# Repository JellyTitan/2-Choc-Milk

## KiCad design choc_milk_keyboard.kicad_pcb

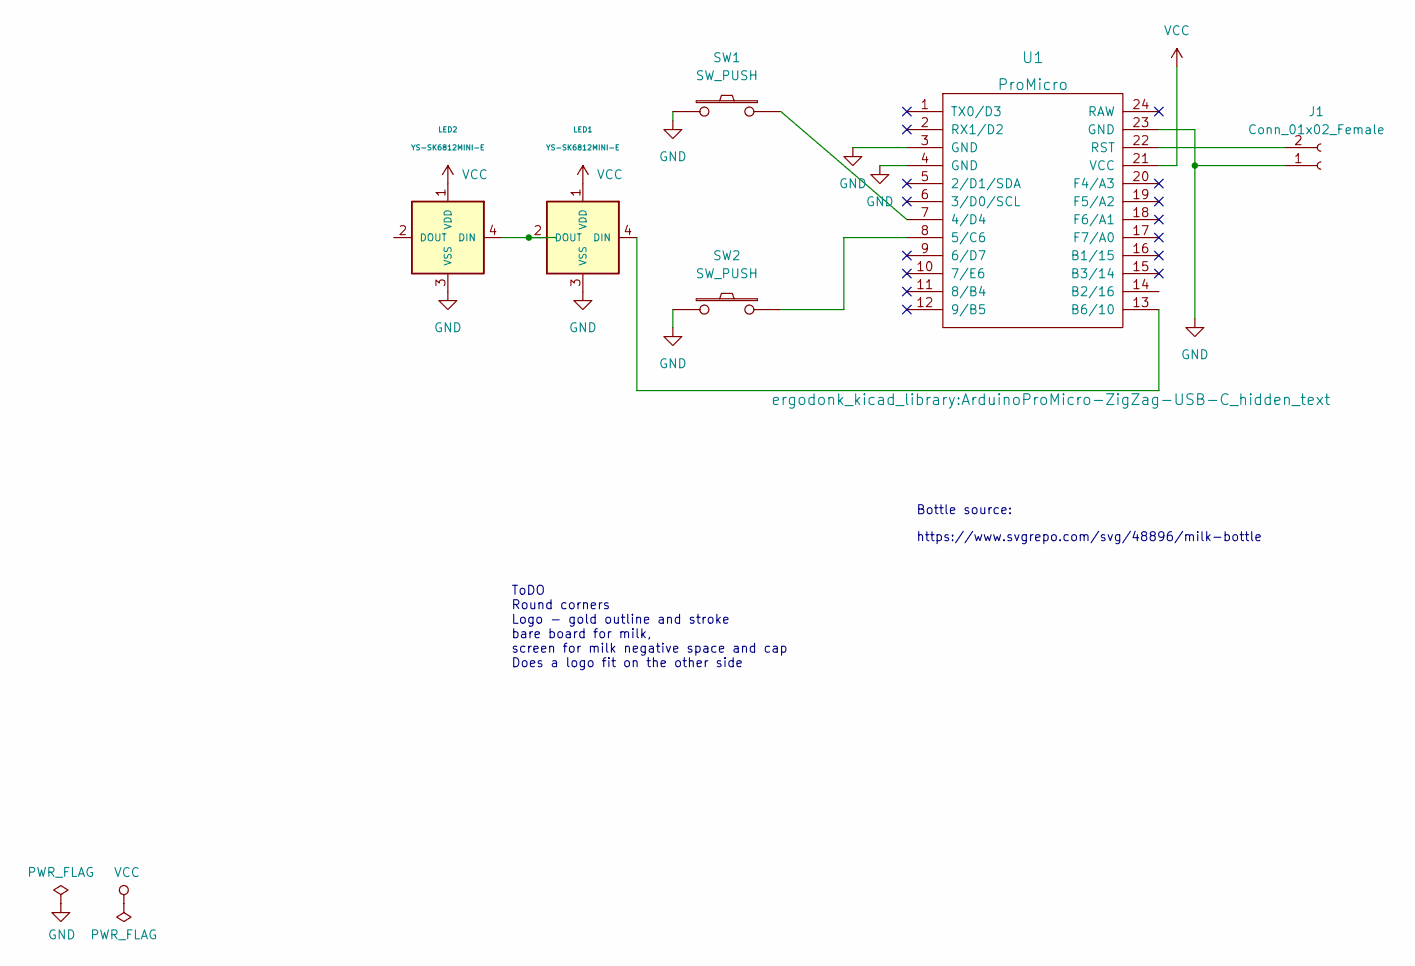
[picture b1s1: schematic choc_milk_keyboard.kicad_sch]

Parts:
J1: Conn_01x02_Female; PinHeader_1x02_P2.54mm_Vertical
LED1, LED2: YS-SK6812MINI-E; SK6812-MINI-E
SW1, SW2: SW_PUSH; Low-Profile-MX-Choc-V1-V2
U1: ProMicro; ArduinoProMicro-ZigZag-USB-C_hidden_text

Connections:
GND: J1.1, LED1.3 (VSS), LED2.3 (VSS), SW1.2, SW2.2, U1.3 (GND), U1.4 (GND), U1.23 (GND)
unnamed: J1.2, U1.22 (RST)
unnamed: LED1.4 (DIN), U1.13 (B6/10)
unnamed: LED1.2 (DOUT), LED2.4 (DIN)
unnamed: SW1.1, U1.7 (4/D4)
unnamed: SW2.1, U1.8 (5/C6)
VCC: LED1.1 (VDD), LED2.1 (VDD), U1.21 (VCC)

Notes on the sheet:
ToDO Round corners Logo - gold outline and stroke bare board for milk, screen for milk negative space and cap Does a logo fit on the other side
https://www.svgrepo.com/svg/48896/milk-bottle
Bottle source:

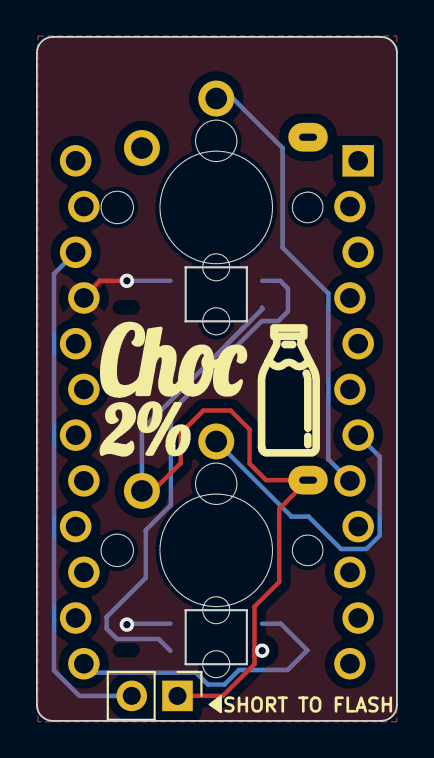
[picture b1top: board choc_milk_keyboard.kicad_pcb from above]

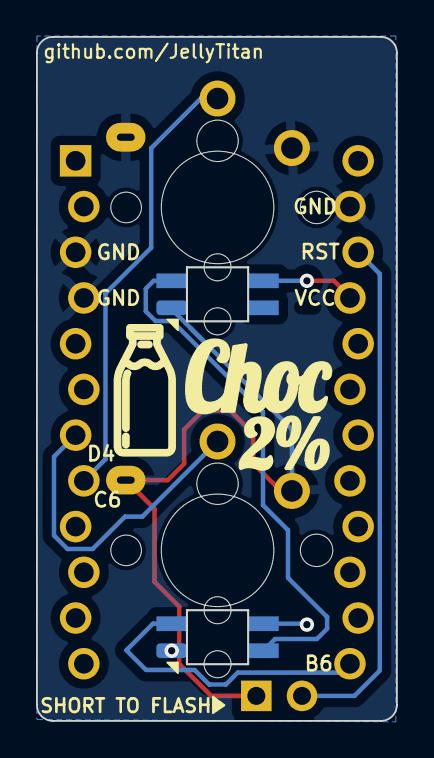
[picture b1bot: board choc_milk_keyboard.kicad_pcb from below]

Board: 2 copper layers, 20.0 x 38.0 mm, 6 parts (3 on the bottom side), 7 nets.

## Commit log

2023-01-27 KiCad created
2023-01-27 Added part library submodules
2023-01-27 Added SpaceboardsHardware origional milk keyboard for reference
2023-01-28 First draft schematic and pcb complete
2023-01-29 Refactored for USB-C ProMicro USB-C is 3mm longer than micro usb Created a new footprint variant
2023-01-29 Added 3d models, flipped pro micro
2023-01-30 Revised Choc footprint and added logo There are 2 Choc V2 variants - one has an extra non-functional pin. Added drawings and added hole to footprint. Flipped switches and Leds to make routing around 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
2023-01-30 Logo tweak for production and added todo list
2023-02-20 Logo rework, rewire to use classic firmware, silkscreeen tidy
2023-02-20 Moved footprints to new library Sent this version out for production Added tweezer holes to LEDs Cleaned up microcontroller footprint
